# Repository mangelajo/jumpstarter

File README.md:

# jumpstarter
jumpstarter is a project designed to enable generic Hardware in the Loop testability for Edge / embedded designs.

# Software Agent

Should enable standard CI tools and pipeline systems (tekton, gitlab, github, Jenkins, etc...) to integrate with the hardware:
 * Load a device image
 * Reboot
 * Gather logs and wait for finish
 * Return results to the CI system
 * Capture power profile during the whole device lifecycle.

# Hardware Agent
One of the components of the project is an Open Hardware board that bridges the Software and Hardware world
of Edge customers. Enabling them to perform Continous Integration of their Hardware and Software.

It's designed to be mounted on 1U 19" Server racks, in the MiniITX format, and should be connected to an
agent that will perform the control loop on the Device Under Test.

## Features

* USB Storage sharing
  * A storage device can be connected to the Testing host, and then passed down to the DUT
  * USB3.1 (up to 10Gbps) capable
  * USB3.0 and 2.0 capable for backwards compatibility
  * Storage device power cycling

* DUT Power management:
  * ON/OFF, Reset, Reboot
  * Measurement and logging in watts (Integration to Kepler)
  * 5-25V power supply support
  * USB-PD power supply support 5-20V with DUT power negotiation
 
* DUT Control (3.3v I/O)
  * UART Serial port TX/RX (for logging and tracing)
  * 4 customizable control signals
  * RESET signal

# Images of release 1.0.0, on prototyping stage

Yes, we are optimistic with versioning!

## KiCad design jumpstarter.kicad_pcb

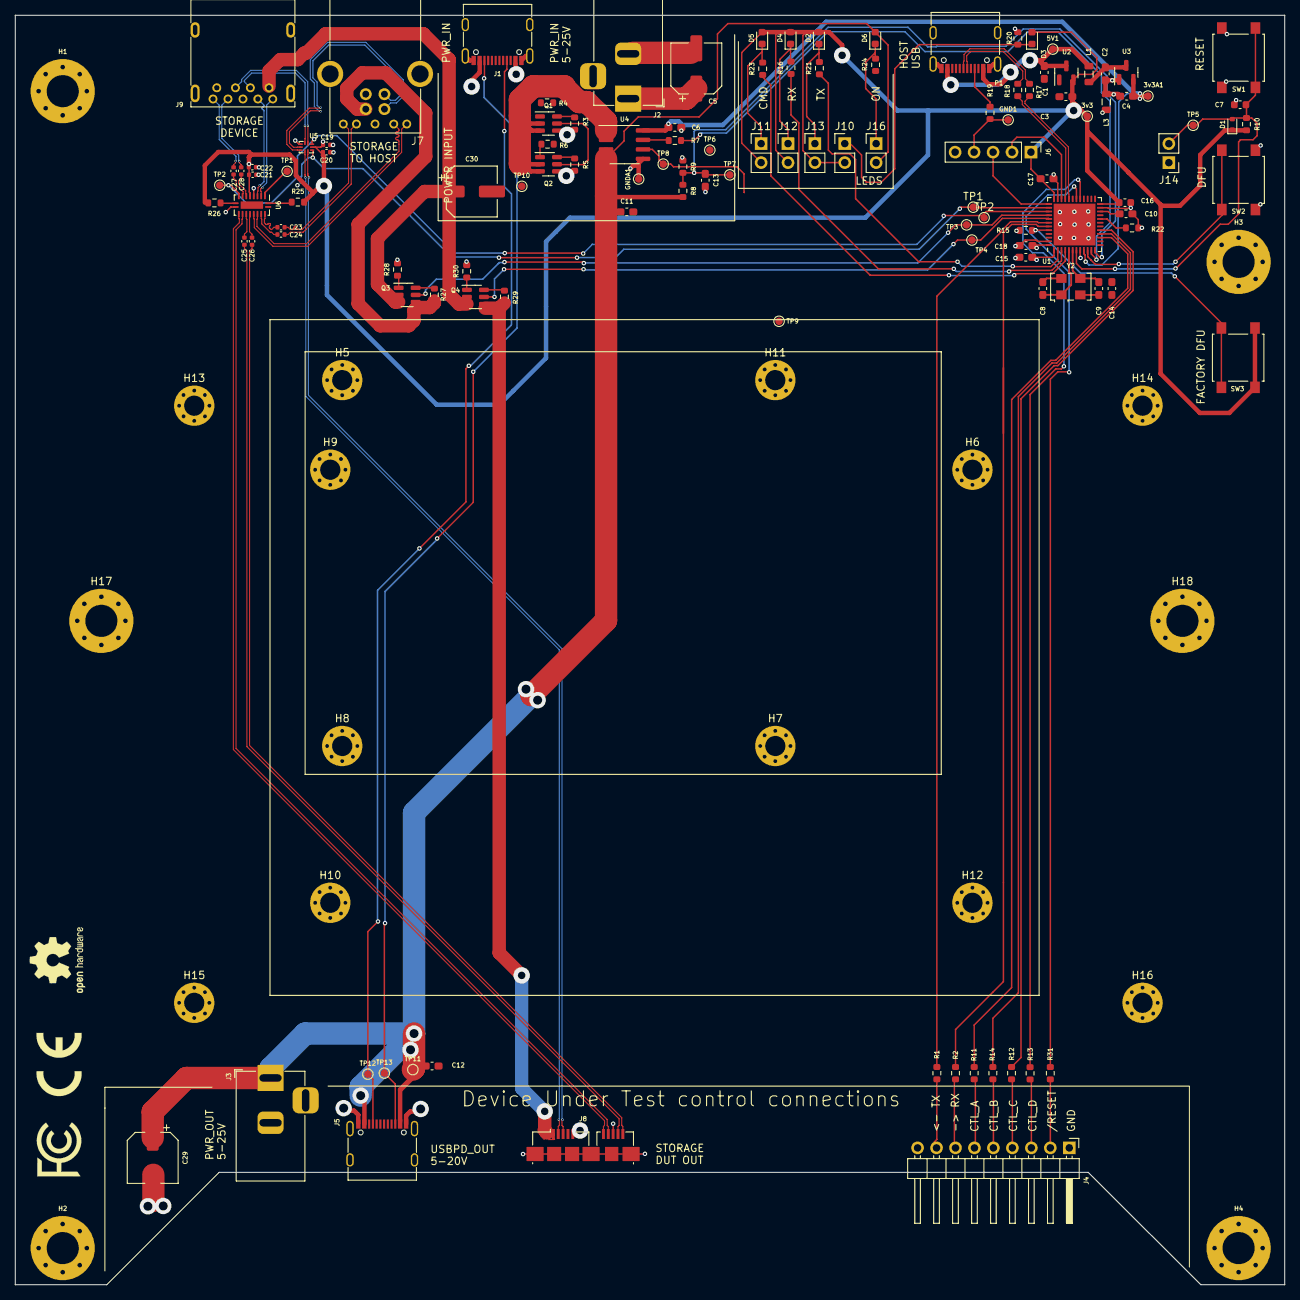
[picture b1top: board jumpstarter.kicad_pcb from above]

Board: 4 copper layers, 170.0 x 170.0 mm, 137 parts (0 on the bottom side), 93 nets.

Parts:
3v3, 3v3A1, 5V1: TestPoint; TestPoint_Pad_D1.0mm
C1, C2, C3, C4, C6, C11, C12: 1uF; C_0603_1608Metric_Pad1.08x0.95mm_HandSolder
C5, C29, C30: 47uF 32V; CP_Elec_6.3x5.4_Nichicon
C7, C16: 100nF; C_0603_1608Metric
C8, C9: 12pF; C_0603_1608Metric_Pad1.08x0.95mm_HandSolder
C10: 2.2uF; C_0603_1608Metric_Pad1.08x0.95mm_HandSolder
C13, C14, C15, C17, C18: 100nF; C_0603_1608Metric_Pad1.08x0.95mm_HandSolder
C19, C21: 1uF; C_0402_1005Metric
C20, C22, C23, C24, C25, C26, C27, C28: 100nF; C_0402_1005Metric
D1: 1N4148WT; D_SOD-523
D2, D3, D4, D5, D6: LED; LED_0603_1608Metric
GND1: TestPoint; TestPoint_Pad_D1.0mm
GNDA1: TestPoint; TestPoint_Pad_D1.0mm
H1, H2, H3, H4, H17, H18: ITX MountingHole; MountingHole_4.3mm_M4_Pad_Via
H5, H6, H7, H8, H9, H10, H11, H12, H13, H14, H15, H16: Board MountingHole; MountingHole_2.7mm_M2.5_Pad_Via
J1, J5: USB_C_Receptacle_PowerOnly_6P; USB_C_Receptacle_G-Switch_GT-USB-7010ASV
J2, J3: Barrel_Jack_MountingPin; BarrelJack_Horizontal
J4: Conn_01x09_Pin; PinHeader_1x09_P2.54mm_Horizontal
J6: Conn_01x05_Pin; PinHeader_1x05_P2.54mm_Vertical
J7: USB3_B; Wurth WR-COM USB 3.0 692221030100
J8: USB3_B_Micro; USB3_Micro-B_Connfly_DS1104-01
J9: USB3_A; USB3_A_Molex_48393-001
J10, J11, J12, J13, J14, J16: Conn_01x02_Pin; PinHeader_1x02_P2.54mm_Vertical
L1, L3: 10uH; L_0805_2012Metric
P1: USB_C_Plug_USB2.0; USB_C_Receptacle_G-Switch_GT-USB-7010ASV
Q1, Q2, Q3, Q4: FDC6330L; TSOT-23-6
R1, R2, R7: 50; R_0603_1608Metric
R3, R5, R27, R29: 47k; R_0603_1608Metric
R4, R6, R28, R30: 2k2; R_0603_1608Metric
R8: 2k4; R_0603_1608Metric
R9: 470; R_0603_1608Metric
R10: 4k7; R_0603_1608Metric
R11, R12, R13, R14, R31: 100; R_0603_1608Metric
R15, R22: 10k; R_0603_1608Metric
R16, R20, R21, R23: 1k; R_0603_1608Metric
R17, R18: 10; R_0603_1608Metric
R19: 5k1; R_0603_1608Metric
R24: 2k; R_0603_1608Metric
R25, R26: 0; R_0603_1608Metric
SW1, SW2, SW3: SW_Push; SW_SPST_B3S-1000
TP1, TP1#2, TP2, TP2#2, TP3, TP4, TP5, TP6, TP7, TP8, TP9, TP10, TP11, TP12, TP13: TestPoint; TestPoint_Pad_D1.0mm
U1: STM32F411CEUx; QFN-48-1EP_7x7mm_P0.5mm_EP5.6x5.6mm
U2, U3: AP2127N-3.3; SOT-23
U4: ACS722xLCTR-20AU; SOIC-8_3.9x4.9mm_P1.27mm
U5: UQFN-10_1.4x1.8mm_P0.4mm
U6: TMUXHS4212; DHVQFN-20-1EP_2.5x4.5mm_P0.5mm_EP1x3mm
Y2: 25 Mhz Crystal; Oscillator_SMD_EuroQuartz_XO53-4Pin_5.0x3.2mm

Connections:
+3.3V: 3v3.1, C3.1, C15.1, C16.1, C17.2, C18.1, C19.1, C20.1, C21.1, C22.1, D1.1 (K), D2.2 (A), D3.2 (A), D4.2 (A), D5.2 (A), J6.1, J10.2, J11.2, J12.2, J13.2, R10.2, R25.2, R26.2, SW3.2, U1.1 (VBAT), U1.24 (VDD), U1.36 (VDD), U1.48 (VDD), U2.2 (VO), U5.9 (3V3), U6.6 (VCC)
+3.3VA: 3v3A1.1, C4.2, C6.1, C14.1, U1.9 (VDDA), U3.2 (VO), U4.8 (VCC)
+5V: 5V1.1, C1.2, L1.2, P1.A4 (VBUS), P1.A9 (VBUS), P1.B4 (VBUS), P1.B9 (VBUS), U2.3 (VI)
+5VA: C2.2, L1.1, U3.3 (VI)
/BOOT0: R15.1, SW3.1, U1.44 (BOOT0)
/BUTTON: SW2.1, U1.10 (PA0)
/BW_SEL: TP8.1, U1.13 (PA3), U4.6 (BW_SEL)
/CTL_A: R11.1, U1.15 (PA5)
/CTL_B: R14.1, U1.16 (PA6)
/CTL_C: R12.1, U1.17 (PA7)
/CTL_D: R13.1, U1.29 (PA8)
/CURRENT_SENSE: R7.2, TP6.1, U1.11 (PA1)
/DN: R17.1, U1.32 (PA11)
/DP: R18.1, U1.33 (PA12)
/LED0: R21.1, U1.2 (PC13)
/LED1: R16.1, U1.3 (PC14)
/LED2: R23.1, U1.4 (PC15)
/NRST: C7.2, D1.2 (A), J14.2, R10.1, SW1.2, TP5.1, U1.7 (NRST)
/ON_OFF: Q1.5 (G1), Q2.5 (G1), TP9.1, U1.14 (PA4)
/RESET: R31.1, U1.30 (PA9)
/RX: J4.7, R2.1
/RX1: R2.2, U1.43 (PB7)
/SWCLK: J6.3, U1.37 (PA14)
/SWDIO: J6.2, U1.34 (PA13)
/TX: J4.8, R1.1
/TX1: R1.2, U1.42 (PB6)
/USB_OEn: TP1.1, TP1#2.1, U1.38 (PA15), U5.8 (OEn), U6.2 (OEn)
/USB_PW_DUT: Q4.5 (G1), TP4.1, U1.41 (PB5)
/USB_PW_HOST: Q3.5 (G1), TP3.1, U1.40 (PB4)
/USB_SEL: TP2.1, TP2#2.1, U1.39 (PB3), U5.10 (SEL), U6.9 (SEL)
/USB_STORAGE_MUX/DUT_DN: J8.2 (D-), U5.6 (DB-)
/USB_STORAGE_MUX/DUT_DP: J8.3 (D+), U5.7 (DB+)
/USB_STORAGE_MUX/DUT_SSRXN: C25.1, J8.9 (SSRX-)
/USB_STORAGE_MUX/DUT_SSRXP: C26.1, J8.10 (SSRX+)
/USB_STORAGE_MUX/DUT_SSTXN: J8.6 (SSTX-), U6.12 (C1n)
/USB_STORAGE_MUX/DUT_SSTXP: J8.7 (SSTX+), U6.13 (C1p)
/USB_STORAGE_MUX/HOST_DN: J7.2 (D-), U5.4 (DA-)
/USB_STORAGE_MUX/HOST_DP: J7.3 (D+), U5.5 (DA+)
/USB_STORAGE_MUX/HOST_SSRXN: C24.1, J7.8 (SSRX-)
/USB_STORAGE_MUX/HOST_SSRXP: C23.1, J7.9 (SSRX+)
/USB_STORAGE_MUX/HOST_SSTXN: J7.5 (SSTX-), U6.16 (B1n)
/USB_STORAGE_MUX/HOST_SSTXP: J7.6 (SSTX+), U6.17 (B1p)
/USB_STORAGE_MUX/STORAGE_DN: J9.2 (D-), U5.2 (D-)
/USB_STORAGE_MUX/STORAGE_DP: J9.3 (D+), U5.1 (D+)
/USB_STORAGE_MUX/STORAGE_SSRXN: C27.2, J9.5 (SSRX-)
/USB_STORAGE_MUX/STORAGE_SSRXP: C28.2, J9.6 (SSRX+)
/USB_STORAGE_MUX/STORAGE_SSTXN: J9.8 (SSTX-), U6.4 (A0n)
/USB_STORAGE_MUX/STORAGE_SSTXP: J9.9 (SSTX+), U6.3 (A0p)
/USB_STORAGE_MUX/VBUS_DUT: J8.1 (VBUS), Q4.4 (S2), R29.1
/USB_STORAGE_MUX/VBUS_HOST: J7.1 (VBUS), Q3.4 (S2), R27.1
/USB_STORAGE_MUX/VBUS_STORAGE: C30.1, J9.1 (VBUS), Q3.2 (D2), Q3.3 (D2), Q4.2 (D2), Q4.3 (D2)
/USB_STORAGE_MUX/_DUT_SSRXN: C25.2, U6.14 (C0n)
/USB_STORAGE_MUX/_DUT_SSRXP: C26.2, U6.15 (C0p)
/USB_STORAGE_MUX/_HOST_SSRXN: C24.2, U6.18 (B0n)
/USB_STORAGE_MUX/_HOST_SSRXP: C23.2, U6.19 (B0p)
/USB_STORAGE_MUX/_STORAGE_SSRXN: C27.1, U6.8 (A1n)
/USB_STORAGE_MUX/_STORAGE_SSRXP: C28.1, U6.7 (A1p)
/VOUT_SENSE: C13.1, R8.1, R9.2, TP7.1, U1.12 (PA2)
/XTALI: C9.2, U1.6 (PH1), Y2.3
/XTALO: C8.2, U1.5 (PH0), Y2.1
/_DN: P1.A7 (D-), R17.2
/_DP: P1.A6 (D+), R18.2
/board_control/CC1: J1.A5 (CC1), J5.A5 (CC1), TP12.1
/board_control/CC2: J1.B5 (CC2), J5.B5 (CC2), TP13.1
/board_control/CTL_A_: J4.6, R11.2
/board_control/CTL_B_: J4.5, R14.2
/board_control/CTL_C_: J4.4, R12.2
/board_control/CTL_D_: J4.3, R13.2
/board_control/RESET_: J4.2, R31.2
/board_control/VCCOUT: C11.1, C12.2, C29.1, D6.2 (A), J3.1, J5.A9 (VBUS), J5.B9 (VBUS), J16.2, R8.2, TP11.1, U4.3 (IP-), U4.4 (IP-)
/board_control/VCCOUT_SW: Q1.2 (D2), Q1.3 (D2), Q2.2 (D2), Q2.3 (D2), TP10.1, U4.1 (IP+), U4.2 (IP+)
/board_control/_CURRENT_SENSE: R7.1, U4.7 (VIOUT)
GND: C1.1, C3.2, C5.2, C7.1, C8.1, C9.1, C10.1, C11.2, C12.1, C13.2, C14.2, C15.2, C16.2, C17.1, C18.2, C19.2, C20.2, C21.2, C22.2, C29.2, C30.2, GND1.1, J1.A12 (GND), J1.B12 (GND), J1.S1 (SHIELD), J2.2, J3.2, J4.1, J5.A12 (GND), J5.B12 (GND), J5.S1 (SHIELD), J6.4, J7.4 (GND), J7.7 (DRAIN), J7.10 (SHIELD), J8.5 (GND), J8.8 (DRAIN), J8.11 (SHIELD), J9.4 (GND), J9.7 (DRAIN), J9.10 (SHIELD), J14.1, L3.2, P1.A1 (GND), P1.A12 (GND), P1.B1 (GND), P1.B12 (GND), P1.S1 (SHIELD), R4.2, R6.1, R15.2, R19.2, R20.1, R22.2, R24.1, R28.2, R30.2, SW1.1, SW2.2, U1.23 (VSS), U1.35 (VSS), U1.47 (VSS), U1.49 (VSS), U2.1 (GND), U5.3 (GND), U6.5 (GND), U6.11 (GND), U6.20 (GND), Y2.2, Y2.4
GNDA: C2.1, C4.1, C6.2, GNDA1.1, L3.1, R9.1, U1.8 (VSSA), U3.1 (GND), U4.5 (GND)
unnamed: D2.1 (K), J13.1, R21.2
unnamed: D3.1 (K), J10.1, R20.2
unnamed: D4.1 (K), J12.1, R16.2
unnamed: D5.1 (K), J11.1, R23.2
unnamed: D6.1 (K), J16.1, R24.2
unnamed: P1.A5 (CC), R19.1
unnamed: Q1.6 (D1), R3.2
unnamed: Q1.1 (S1), R4.1
unnamed: Q2.6 (D1), R5.2
unnamed: Q2.1 (S1), R6.2
unnamed: Q3.6 (D1), R27.2
unnamed: Q3.1 (S1), R28.1
unnamed: Q4.6 (D1), R29.2
unnamed: Q4.1 (S1), R30.1
unnamed: R22.1, U1.20 (PB2)
unnamed: C10.2, U1.22 (VCAP1)
unnamed: R25.1, U6.1 (RSVD1)
unnamed: R26.1, U6.10 (RSVD2)
VCC: C5.1, J1.A9 (VBUS), J1.B9 (VBUS), J2.1, Q1.4 (S2), Q2.4 (S2), R3.1, R5.1

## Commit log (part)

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2023-06-17 Mounting holes positioned, and routing
